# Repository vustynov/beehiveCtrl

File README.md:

# beehiveCtrl

### Brief
This project can be interesting for amateur beekeeping. The project is designed to monitor the temperature and control the heating of beehives remotely. The device and software can also be used to control temperature control in other projects, such as an incubator.

The device is based on the microcontroller [ESP8266](http://www.esp8266.com) and firmware [NodeMCU](https://en.wikipedia.org/wiki/NodeMCU).

### Features
 * Remote control the temperature in the hive via browser on your computer, smartphone, tablets
 * Remote set the parameters of heater (minimal and maximal temperature)
 * Transfer of the temperature and the current status of the heater to the [thingspeak.com](http://thingspeak.com) every X minutes
 * Builds the [charts](https://thingspeak.com/channels/185299)
 * Once set up, the device can work offline, without internet connection.

### Schems and Circuit board
Directory **board** contains schematic and circuit board of device developed in [EAGLE](https://www.autodesk.com/products/eagle/overview). 
The scheme is very simple. It consists the power regulatots (LM7805 and 1117S33) for the relay coil and microcontroller. To switch on the relay a driver is used the BC546 transistor.

### Source code
Directory **src** contains the source code of the project, wroted on Lua and based on [NodeMCU API](https://nodemcu.readthedocs.io/en/master/).

### How to build
1. Build the board according to the schematic diagram showed on **board/BeeTermostat.sch**
2. Connect *+12-18V* power to *X1* connector on your board without installing the ESP8266 and check the correctness of the voltage at the points of the circuit where the power of the microcontroller must be approached. It should be the "3.3V".
3. Power off your board, install the ESP8266 to the socket on the board, and connect the **JP3** (TX,RX,GND) connector to the computer via USB-TTL adapter. For example, you can use [this device](http://www.instructables.com/id/USB-to-TTL-Converter-PL2303HX/) for that.
4. Power on your board and check the WiFi new access points in you environment. You should discover a new access point with a default name (installed by [Expressif](https://www.espressif.com/) ).
5. Build and download the NodeMCU firmware from the [nodemcu-build.com](https://nodemcu-build.com/) Choose the following modules:
 - DS18B20
 - file
 - GPIO
 - net
 - node
 - 1-wire
 - timer
 - UART
 - WiFi
 - float

6. Install the NodeMCU firmware to microcontroller. Under Linux you can use the [esptool](https://github.com/espressif/esptool) (read this [esp-linux-guide](http://www.whatimade.today/flashing-the-nodemcu-firmware-on-the-esp8266-linux-guide/) for that. Example of install:
```
$ sudo ./esptool-master/esptool.py --port /dev/ttyUSB0 --baud 460800 write_flash --flash_size 32m -fm dio 0x00000 ./nodemcu-master-10-modules-2017-09-25-18-22-58-float.bin
```

7. Install the [ESPlorer](https://esp8266.ru/esplorer/) or some another tools for working with NodeMCU to your computer.
8. Upload the lua scripts from directory **src** to your ESP microcontoller by using the ESPlorer or some another tools.
9. Restart module, find new WiFi access point *beehive* and try to connect to this AP with password *11111111*. You can change *SID* and *password* before in the **src/bc-init.cfg**.
10. If connect is successfull, try to open http://192.168.2.1 in your browser. You sould see the page with configuration of your beehive controller.
11. Try to change the temperature settings and check your heater.

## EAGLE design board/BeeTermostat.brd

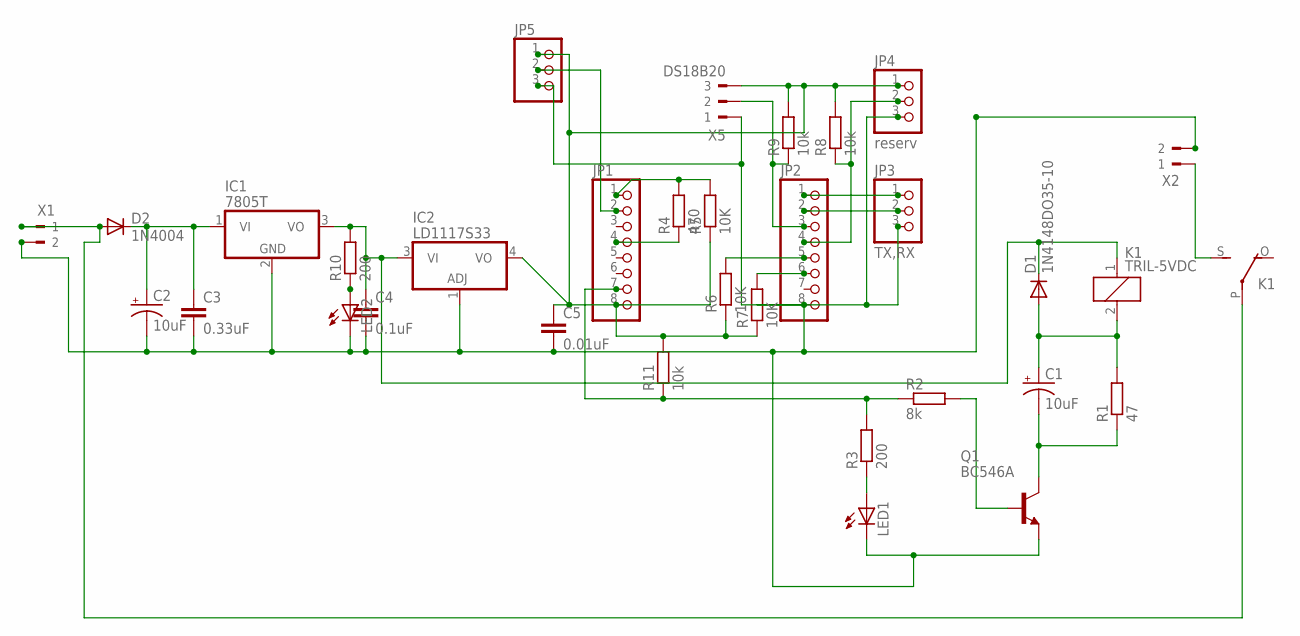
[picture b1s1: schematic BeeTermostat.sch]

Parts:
C1, C2: 10uF; E2,5-5
C3: 0.33uF; C050-025X075
C4: 0.1uF; C050-025X075
C5: 0.01uF; C0805
D1: 1N4148DO35-10; DO35-10
D2: 1N4004; DO41-10
IC1: 7805T; TO220H
IC2: LD1117S33; SOT223
JP1, JP2: PINHD-1X8; 1X08
JP3: TX,RX; 1X03
JP4: reserv; 1X03
JP5: PINHD-1X3; 1X03
K1: TRIL-5VDC; E3206S
LED1, LED2: LED5MM
Q1: BC546A; TO92-EBC
R1: 47; 0309/12
R2: 8k; 0309/12
R3: 200; 0309/12
R4: 470; M0805
R5, R6, R7: 10K; M0805
R8, R9, R11: 10k; M0805
R10: 200; 0207/10
X1, X2: 90-2
X5: DS18B20; 90-3

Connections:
unnamed: C1.+, D1.A, K1.2, R1.2
unnamed: C1.-, Q1.C, R1.1
unnamed: Q1.B, R2.2
unnamed: JP1.7, R2.1, R3.2, R11.1
unnamed: LED1.A, R3.1
unnamed: C2.+, C3.1, D2.C, IC1.1 (VI)
unnamed: C4.1, D1.C, IC1.3 (VO), IC2.3 (VI), K1.1, R10.2
unnamed: JP2.3, R9.1, X5.2
unnamed: JP2.1, JP3.1
unnamed: K1.S, X2.1
unnamed: JP2.2, JP3.2
unnamed: C2.-, C3.2, C4.2, C5.2, IC1.2 (GND), IC2.1 (ADJ), JP2.8, JP3.3, JP4.3, JP5.3, LED1.K (C), LED2.K (C), Q1.E, X1.2, X2.2, X5.1
unnamed: JP2.5, R6.2
unnamed: JP1.4, R4.1
unnamed: JP1.1, R4.2, R5.2
unnamed: JP2.6, R7.2
unnamed: D2.A, K1.P, X1.1
unnamed: JP2.4, JP4.2, R8.1
unnamed: C5.1, IC2.4 (VO), JP1.8, JP4.1, JP5.1, R5.1, R6.1, R7.1, R8.2, R9.2, R11.2, X5.3
unnamed: JP1.2, JP5.2
unnamed: LED2.A, R10.1

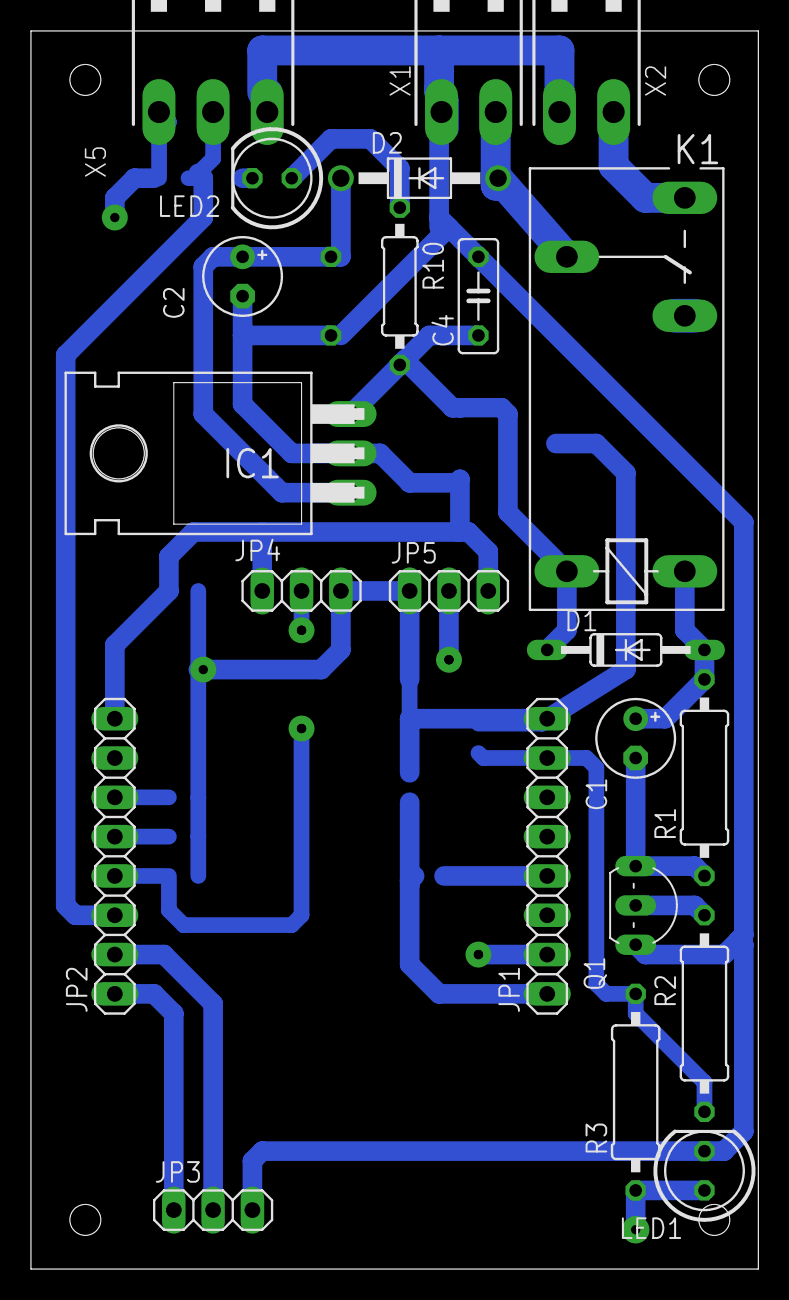
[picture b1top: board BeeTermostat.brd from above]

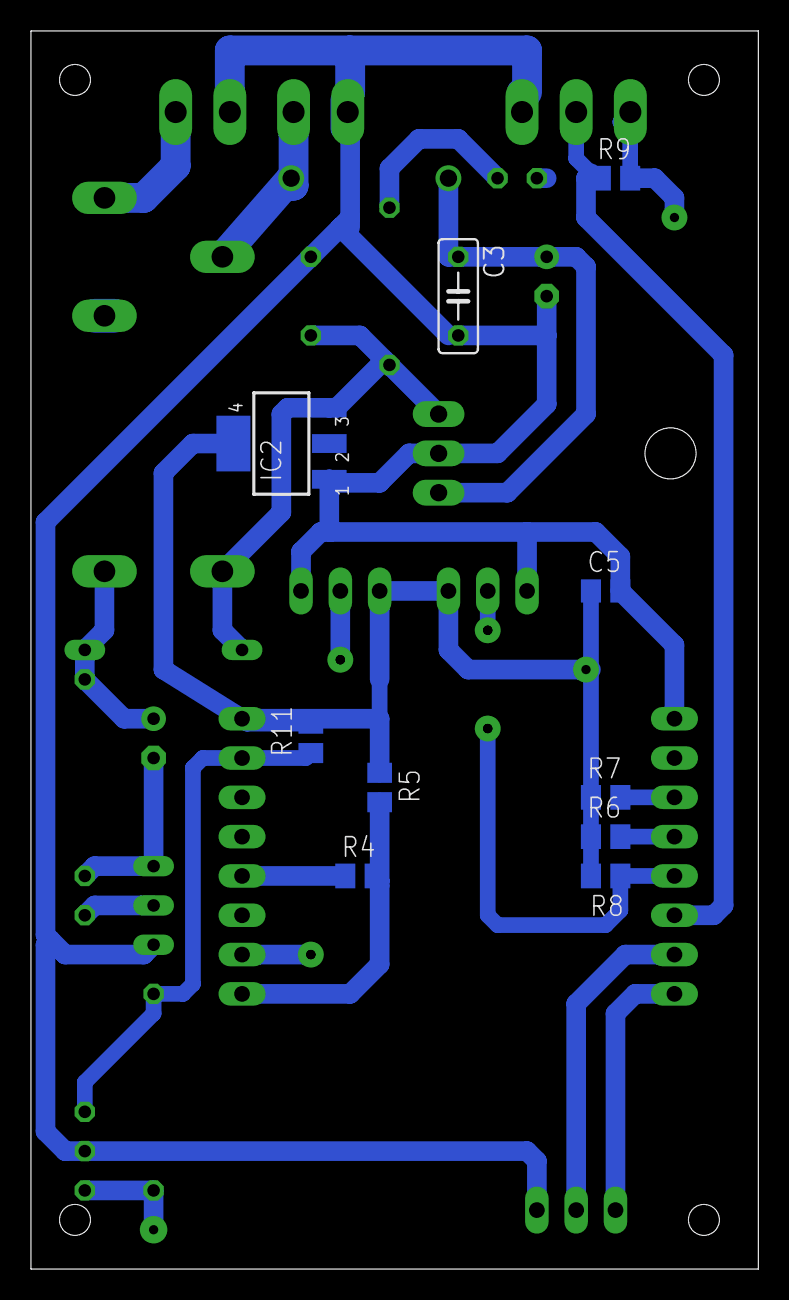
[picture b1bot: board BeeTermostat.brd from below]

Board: 2 copper layers, 47.0 x 80.0 mm, 32 parts (10 on the bottom side), 21 nets.

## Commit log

2017-11-27 readme update
2017-11-28 pcb added
2018-01-30 added new files to project
2018-01-31 added How to build instruction
2018-01-31 update def params
2018-01-31 image of schem added
2018-01-31 new images added
2018-02-01 added details
2018-02-01 brif for schem added
2018-02-01 link to charts added
